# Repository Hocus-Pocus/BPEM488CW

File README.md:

# BPEM488CW
Hardware for the BPEM488CW project

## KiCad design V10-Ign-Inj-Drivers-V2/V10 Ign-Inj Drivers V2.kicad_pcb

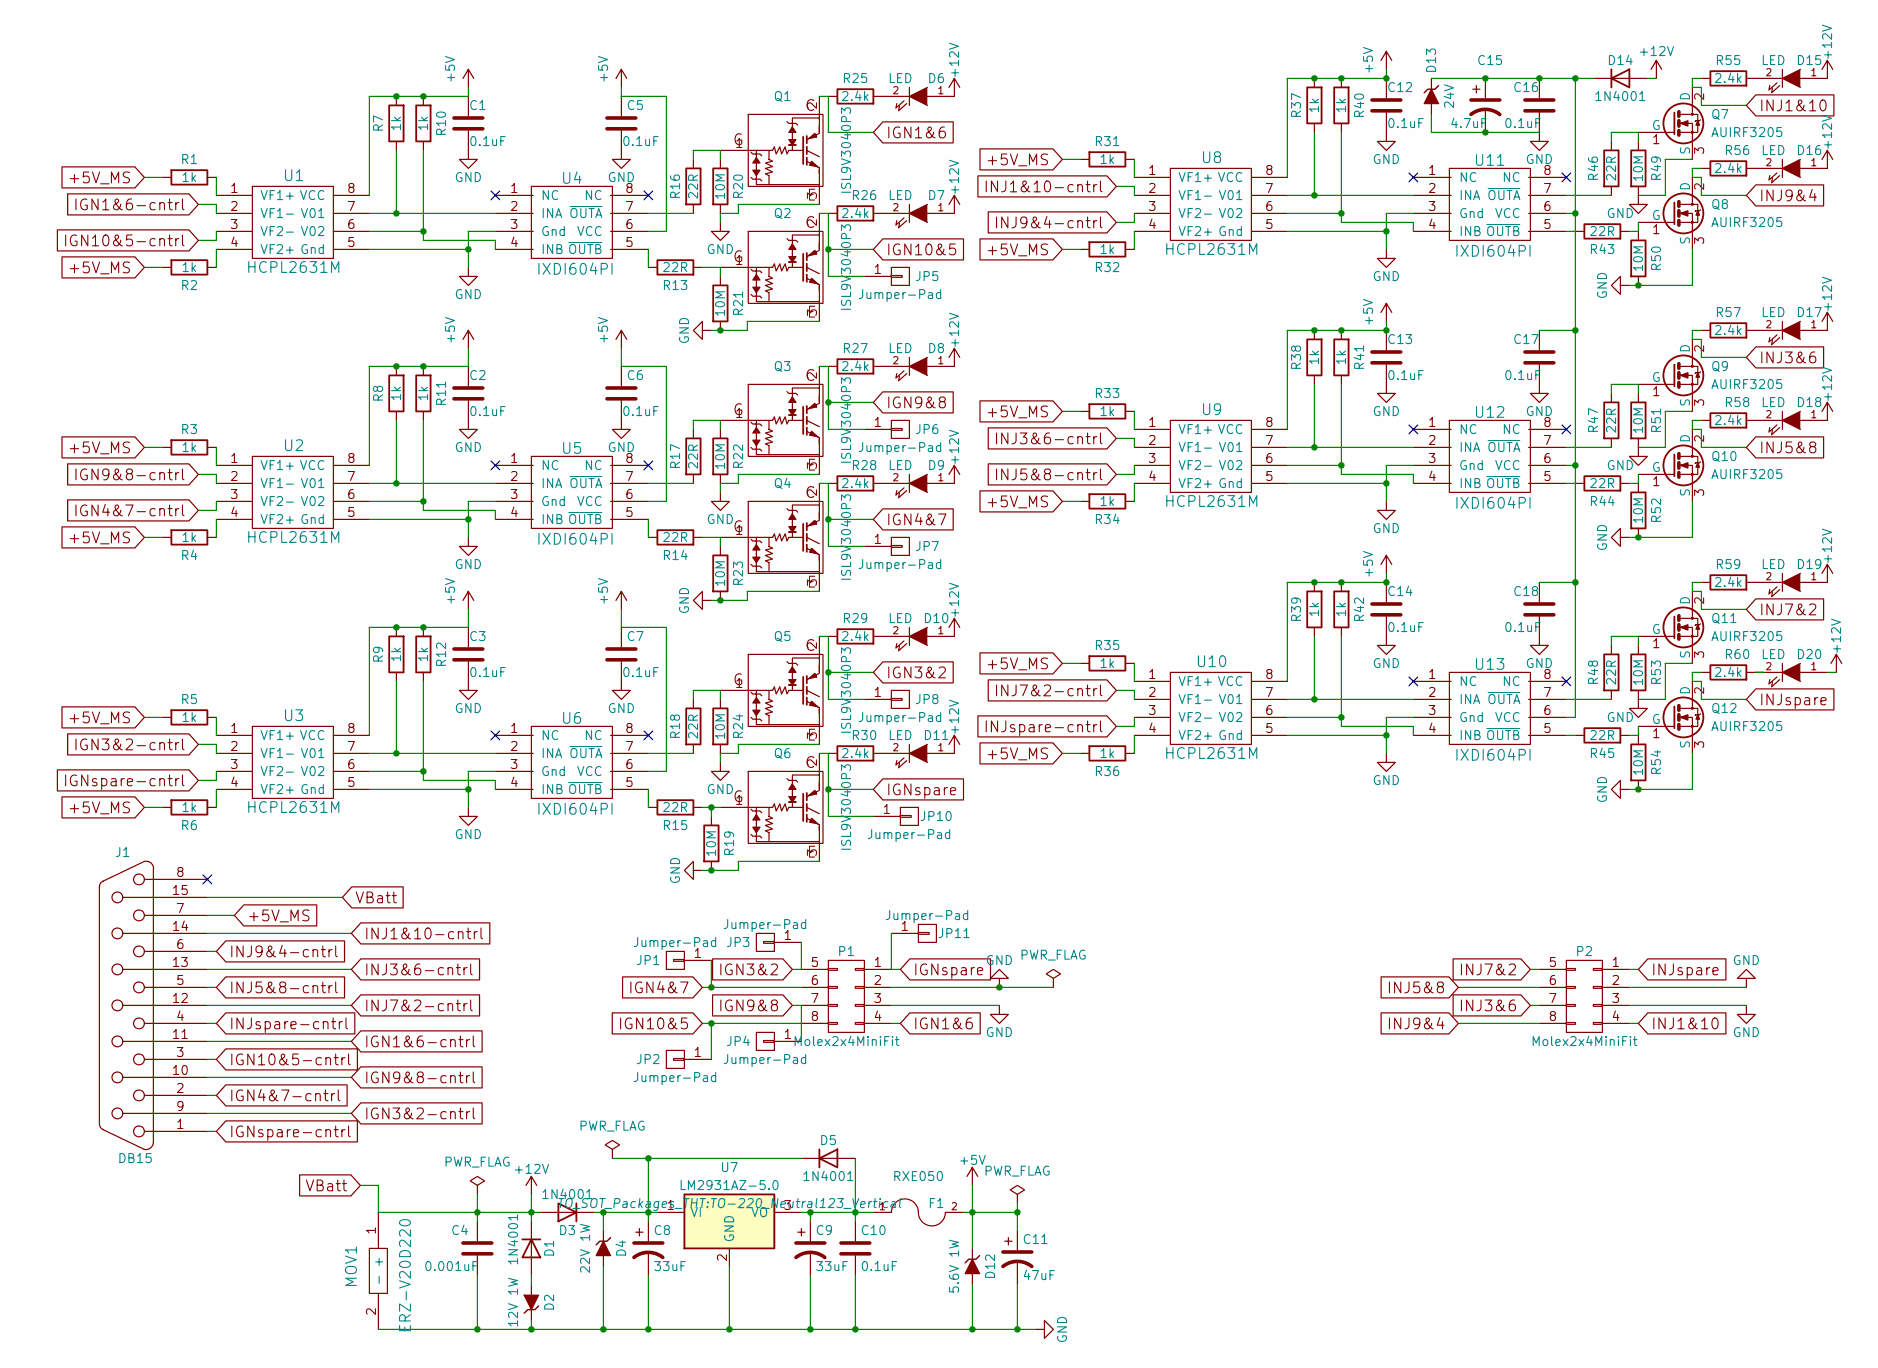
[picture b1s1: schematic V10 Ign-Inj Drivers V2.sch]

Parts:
C1, C2, C3, C5, C6, C7, C10, C12, C13, C14, C16, C17, C18: 0.1uF; C_Disc_D3_P2.5
C4: 0.001uF; C_Disc_D6_P5
C8, C9: 33uF; C_Radial_D10_L13_P5
C11: 47uF; C_Radial_D10_L13_P5
C15: 4.7uF; C_Radial_D5_L6_P2.5
D1, D3, D5, D14: 1N4001; Diode_DO-41_SOD81_Horizontal_RM10
D2: 12V 1W; Diode_DO-41_SOD81_Horizontal_RM10
D4: 22V 1W; Diode_DO-41_SOD81_Horizontal_RM10
D6, D7, D8, D9, D10, D11, D15, D16, D17, D18, D19, D20: LED; LED-3MM
D12: 5.6V 1W; Diode_DO-41_SOD81_Horizontal_RM10
D13: 24V; Diode_DO-41_SOD81_Horizontal_RM10
F1: RXE050; C_Disc_D6_P5
J1: DB15; DB15FC
JP1, JP2, JP3, JP4, JP5, JP6, JP7, JP8, JP10, JP11: Jumper-Pad; 1pin
MOV1: ERZ-V20D220; C_Disc_D3_P2.5
P1, P2: Molex2x4MiniFit; Molex_MiniFit-JR-5569-08A2_2x04x4.20mm_Angled
Q1, Q2, Q3, Q4, Q5, Q6: ISL9V3040P3; TO-220_Neutral123_Vertical
Q7, Q8, Q9, Q10, Q11, Q12: AUIRF3205; TO-220_Neutral123_Vertical
R1, R2, R3, R4, R5, R6, R7, R8, R9, R10, R11, R12, R31, R32, R33, R34, R35, R36, R37, R38, R39, R40, R41, R42: 1k; Resistor_Horizontal_RM7mm
R13, R14, R15, R16, R17, R18, R43, R44, R45, R46, R47, R48: 22R; Resistor_Horizontal_RM10mm
R19, R20, R21, R22, R23, R24, R49, R50, R51, R52, R53, R54: 10M; Resistor_Horizontal_RM7mm
R25, R26, R27, R28, R29, R30, R55, R56, R57, R58, R59, R60: 2.4k; Resistor_Horizontal_RM7mm
U1, U2, U3, U8, U9, U10: HCPL2631M; DIP-8_W7.62mm
U4, U5, U6, U11, U12, U13: IXDI604PI; DIP-8_W7.62mm
U7: LM2931AZ-5.0; TO-220_Neutral123_Vertical

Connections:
+5V: C1.1, C2.1, C3.1, C5.1, C6.1, C7.1, C11.1, C12.1, C13.1, C14.1, D12.1 (K), F1.2, R7.2, R8.2, R9.2, R10.2, R11.2, R12.2, R37.2, R38.2, R39.2, R40.2, R41.2, R42.2, U1.8 (VCC), U2.8 (VCC), U3.8 (VCC), U4.6 (VCC), U5.6 (VCC), U6.6 (VCC), U8.8 (VCC), U9.8 (VCC), U10.8 (VCC)
+5V_MS: J1.7, R1.2, R2.2, R3.2, R4.2, R5.2, R6.2, R31.2, R32.2, R33.2, R34.2, R35.2, R36.2
GND: C1.2, C2.2, C3.2, C4.2, C5.2, C6.2, C7.2, C8.2, C9.2, C10.2, C11.2, C12.2, C13.2, C14.2, C15.2, C16.2, C17.2, C18.2, D2.1 (K), D4.2 (A), D12.2 (A), D13.2 (A), MOV1.2 (-), P1.2, P1.3, P2.2, P2.3, Q1.3 (E), Q2.3 (E), Q3.3 (E), Q4.3 (E), Q5.3 (E), Q6.3 (E), Q7.3 (S), Q8.3 (S), Q9.3 (S), Q10.3 (S), Q11.3 (S), Q12.3 (S), R19.2, R20.2, R21.2, R22.2, R23.2, R24.2, R49.2, R50.2, R51.2, R52.2, R53.2, R54.2, U1.5 (Gnd), U2.5 (Gnd), U3.5 (Gnd), U4.3 (Gnd~), U5.3 (Gnd~), U6.3 (Gnd~), U7.2 (GND), U8.5 (Gnd), U9.5 (Gnd), U10.5 (Gnd), U11.3 (Gnd~), U12.3 (Gnd~), U13.3 (Gnd~)
IGN1&6: P1.4, Q1.2 (C), R25.1
IGN1&6-cntrl: J1.11 (P111), U1.2 (VF1-)
IGN3&2: JP3.1, JP8.1, P1.5, Q5.2 (C), R29.1
IGN3&2-cntrl: J1.9, U3.2 (VF1-)
IGN4&7: JP1.1, JP7.1, P1.6, Q4.2 (C), R28.1
IGN4&7-cntrl: J1.2, U2.3 (VF2-)
IGN9&8: JP4.1, JP6.1, P1.7, Q3.2 (C), R27.1
IGN9&8-cntrl: J1.10, U2.2 (VF1-)
IGN10&5: JP2.1, JP5.1, P1.8, Q2.2 (C), R26.1
IGN10&5-cntrl: J1.3, U1.3 (VF2-)
IGNspare: JP10.1, JP11.1, P1.1, Q6.2 (C), R30.1
IGNspare-cntrl: J1.1, U3.3 (VF2-)
INJ1&10: P2.4, Q7.2 (D), R55.1
INJ1&10-cntrl: J1.14, U8.2 (VF1-)
INJ3&6: P2.7, Q9.2 (D), R57.1
INJ3&6-cntrl: J1.13, U9.2 (VF1-)
INJ5&8: P2.6, Q10.2 (D), R58.1
INJ5&8-cntrl: J1.5, U9.3 (VF2-)
INJ7&2: P2.5, Q11.2 (D), R59.1
INJ7&2-cntrl: J1.12, U10.2 (VF1-)
INJ9&4: P2.8, Q8.2 (D), R56.1
INJ9&4-cntrl: J1.6, U8.3 (VF2-)
INJspare: P2.1, Q12.2 (D), R60.1
INJspare-cntrl: J1.4, U10.3 (VF2-)
unnamed: C8.1, D3.1 (K), D4.1 (K), D5.1 (K), U7.1 (VI)
unnamed: C9.1, C10.1, D5.2 (A), F1.1, U7.3 (VO)
unnamed: C15.1, C16.1, C17.1, C18.1, D13.1 (K), D14.1 (K), U11.6 (VCC), U12.6 (VCC), U13.6 (VCC)
unnamed: D1.2 (A), D2.2 (A)
unnamed: D6.2 (K), R25.2
unnamed: D7.2 (K), R26.2
unnamed: D8.2 (K), R27.2
unnamed: D9.2 (K), R28.2
unnamed: D10.2 (K), R29.2
unnamed: D11.2 (K), R30.2
unnamed: D15.2 (K), R55.2
unnamed: D16.2 (K), R56.2
unnamed: D17.2 (K), R57.2
unnamed: D18.2 (K), R58.2
unnamed: D19.2 (K), R59.2
unnamed: D20.2 (K), R60.2
unnamed: Q1.1 (G), R16.1, R20.1
unnamed: Q2.1 (G), R13.2, R21.1
unnamed: Q3.1 (G), R17.1, R22.1
unnamed: Q4.1 (G), R14.2, R23.1
unnamed: Q5.1 (G), R18.1, R24.1
unnamed: Q6.1 (G), R15.2, R19.1
unnamed: Q7.1 (G), R46.1, R49.1
unnamed: Q8.1 (G), R43.2, R50.1
unnamed: Q9.1 (G), R47.1, R51.1
unnamed: Q10.1 (G), R44.2, R52.1
unnamed: Q11.1 (G), R48.1, R53.1
unnamed: Q12.1 (G), R45.2, R54.1
unnamed: R1.1, U1.1 (VF1+)
unnamed: R2.1, U1.4 (VF2+)
unnamed: R3.1, U2.1 (VF1+)
unnamed: R4.1, U2.4 (VF2+)
unnamed: R5.1, U3.1 (VF1+)
unnamed: R6.1, U3.4 (VF2+)
unnamed: R7.1, U1.7 (V01), U4.2 (INA)
unnamed: R8.1, U2.7 (V01), U5.2 (INA)
unnamed: R9.1, U3.7 (V01), U6.2 (INA)
unnamed: R10.1, U1.6 (V02), U4.4 (INB)
unnamed: R11.1, U2.6 (V02), U5.4 (INB)
unnamed: R12.1, U3.6 (V02), U6.4 (INB)
unnamed: R13.1, U4.5 (~OUTB)
unnamed: R14.1, U5.5 (~OUTB)
unnamed: R15.1, U6.5 (~OUTB)
unnamed: R16.2, U4.7 (~OUTA)
unnamed: R17.2, U5.7 (~OUTA)
unnamed: R18.2, U6.7 (~OUTA)
unnamed: R31.1, U8.1 (VF1+)
unnamed: R32.1, U8.4 (VF2+)
unnamed: R33.1, U9.1 (VF1+)
unnamed: R34.1, U9.4 (VF2+)
unnamed: R35.1, U10.1 (VF1+)
unnamed: R36.1, U10.4 (VF2+)
unnamed: R37.1, U8.7 (V01), U11.2 (INA)
unnamed: R38.1, U9.7 (V01), U12.2 (INA)
unnamed: R39.1, U10.7 (V01), U13.2 (INA)
unnamed: R40.1, U8.6 (V02), U11.4 (INB)
unnamed: R41.1, U9.6 (V02), U12.4 (INB)
unnamed: R42.1, U10.6 (V02), U13.4 (INB)
unnamed: R43.1, U11.5 (~OUTB)
unnamed: R44.1, U12.5 (~OUTB)
unnamed: R45.1, U13.5 (~OUTB)
unnamed: R46.2, U11.7 (~OUTA)
unnamed: R47.2, U12.7 (~OUTA)
unnamed: R48.2, U13.7 (~OUTA)
VBatt: C4.1, D1.1 (K), D3.2 (A), D6.1 (A), D7.1 (A), D8.1 (A), D9.1 (A), D10.1 (A), D11.1 (A), D14.2 (A), D15.1 (A), D16.1 (A), D17.1 (A), D18.1 (A), D19.1 (A), D20.1 (A), J1.15, MOV1.1 (+)

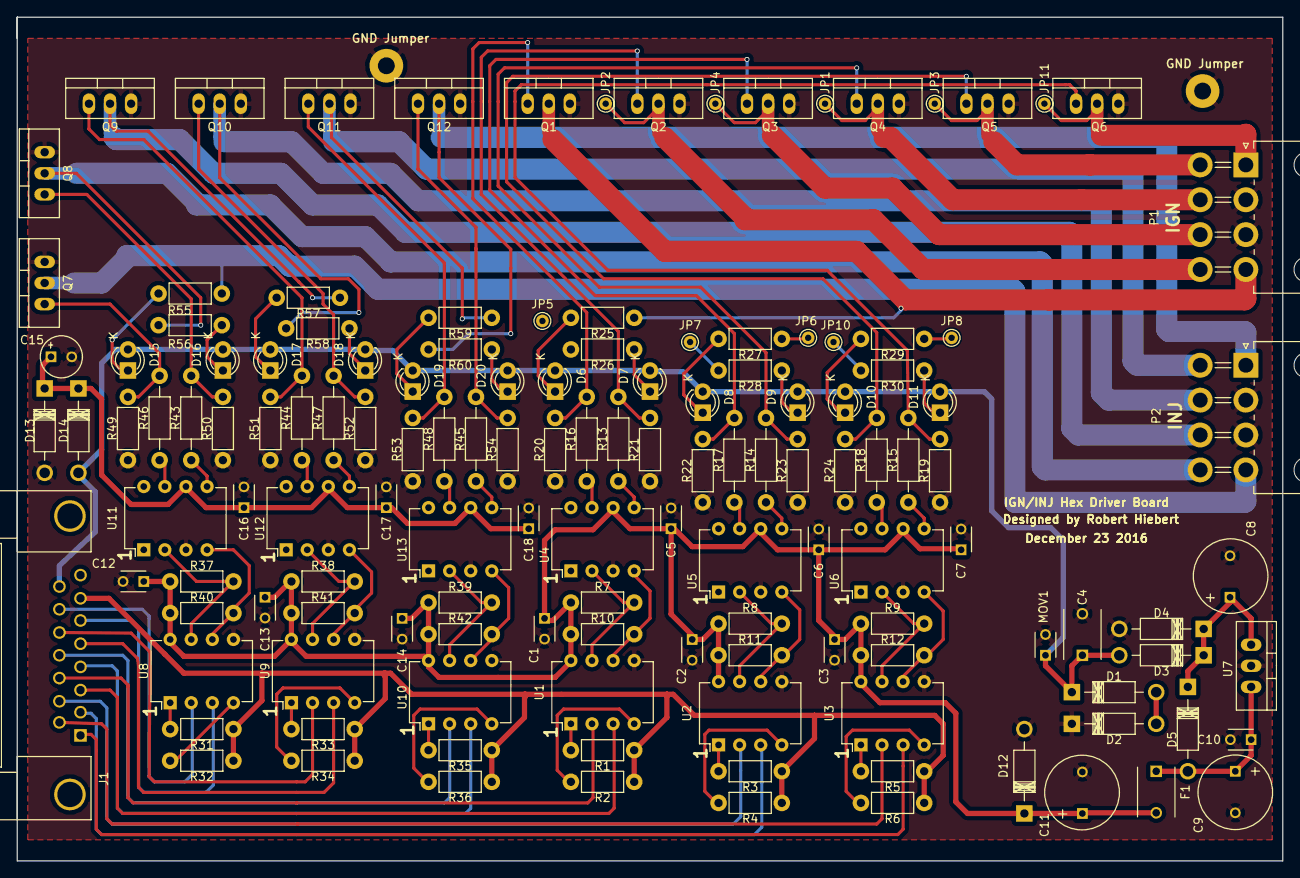
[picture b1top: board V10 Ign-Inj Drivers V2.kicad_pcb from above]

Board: 2 copper layers, 152.4 x 101.6 mm, 138 parts (0 on the bottom side), 92 nets.

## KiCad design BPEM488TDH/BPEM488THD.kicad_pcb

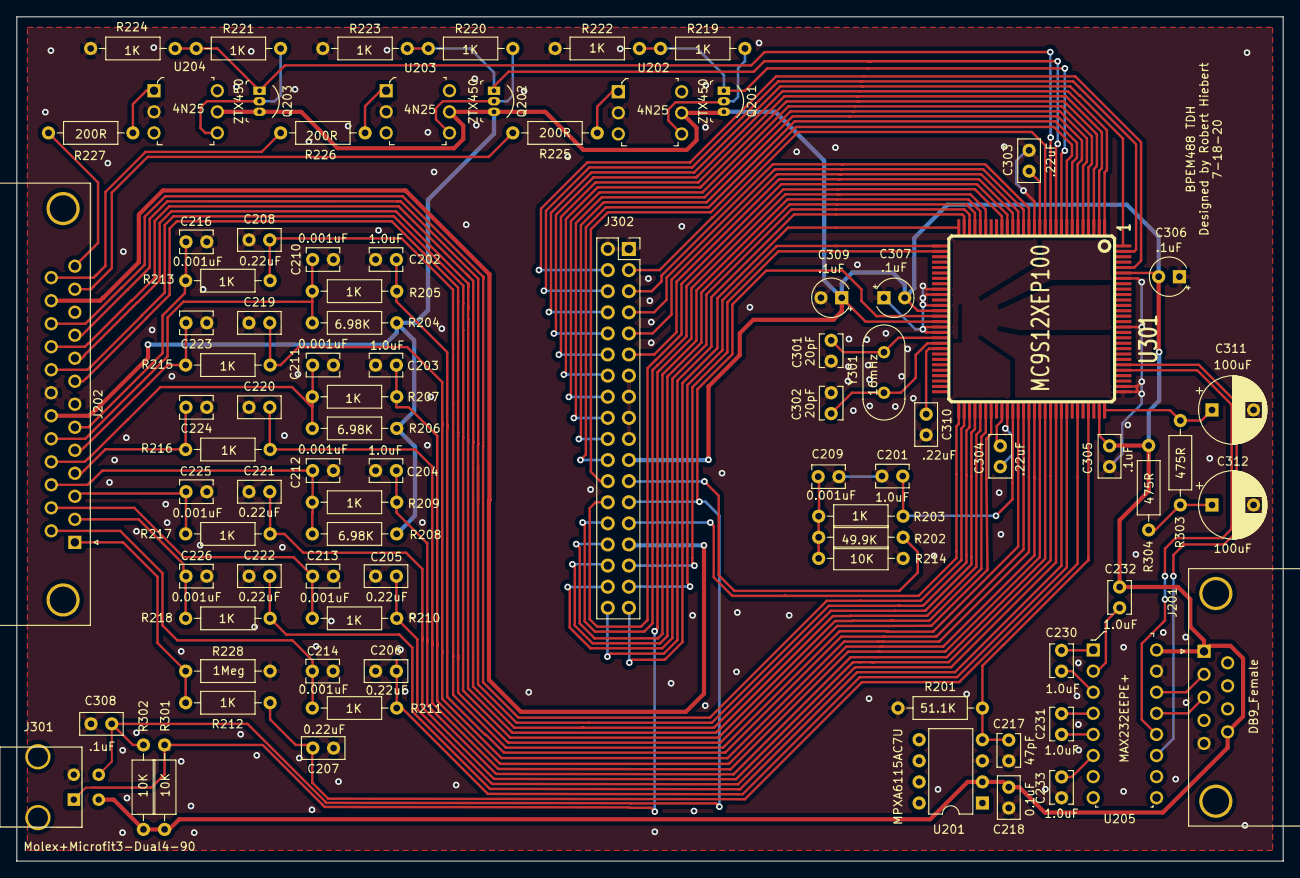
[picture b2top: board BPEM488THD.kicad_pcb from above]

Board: 2 copper layers, 152.4 x 101.6 mm, 87 parts (0 on the bottom side), 92 nets.

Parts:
C201, C202, C203, C204, C230, C231, C232, C233: 1.0uF; C_Disc_D3.8mm_W2.6mm_P2.50mm
C205, C206, C207, C208, C219, C220, C221, C222: 0.22uF; C_Disc_D5.0mm_W2.5mm_P2.50mm
C209, C210, C211, C212, C213, C214, C216, C223, C224, C225, C226: 0.001uF; C_Disc_D3.8mm_W2.6mm_P2.50mm
C217: 47pF; C_Disc_D3.8mm_W2.6mm_P2.50mm
C218: 0.1uF; C_Disc_D5.0mm_W2.5mm_P2.50mm
C301, C302: 20pF; C_Disc_D3.8mm_W2.6mm_P2.50mm
C303, C304, C310: .22uF; C_Disc_D5.0mm_W2.5mm_P2.50mm
C305, C308: .1uF; C_Disc_D5.0mm_W2.5mm_P2.50mm
C306, C307, C309: .1uF; CP_Radial_Tantal_D4.5mm_P2.50mm
C311, C312: 100uF; CP_Radial_D8.0mm_P5.00mm
J201: DB9_Female; DSUB-9_Female_Horizontal_P2.77x2.84mm_EdgePinOffset9.90mm_H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
J202: DB25_Female; DSUB-25_Female_Horizontal_P2.77x2.84mm_EdgePinOffset7.70mm_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
J301: Molex+Microfit3-Dual4-90; Molex-Microfit3-Dual4-90
J302: Conn_02x18_Odd_Even; PinSocket_2x18_P2.54mm_Vertical
Q201, Q202, Q203: ZTX450; TO-92-3
R201: 51.1K; R_Axial_DIN0207_L6.3mm_D2.5mm_P10.16mm_Horizontal
R202: 49.9K; R_Axial_DIN0207_L6.3mm_D2.5mm_P10.16mm_Horizontal
R203, R205, R207, R209, R210, R211, R212, R213, R215, R216, R217, R218, R219, R220, R221, R222, R223, R224: 1K; R_Axial_DIN0207_L6.3mm_D2.5mm_P10.16mm_Horizontal
R204, R206, R208: 6.98K; R_Axial_DIN0207_L6.3mm_D2.5mm_P10.16mm_Horizontal
R214, R301, R302: 10K; R_Axial_DIN0207_L6.3mm_D2.5mm_P10.16mm_Horizontal
R225, R226, R227: 200R; R_Axial_DIN0207_L6.3mm_D2.5mm_P10.16mm_Horizontal
R228: 1Meg; R_Axial_DIN0207_L6.3mm_D2.5mm_P10.16mm_Horizontal
R303, R304: 475R; R_Axial_DIN0207_L6.3mm_D2.5mm_P10.16mm_Horizontal
U201: MPXA6115AC7U; DIP-8_W7.62mm
U202, U203, U204: 4N25; DIP-6_W7.62mm
U205: MAX232EEPE+; DIP-16_W7.62mm
U301: MC9S12XEP100; PQFP112
Y301: 16mHz; Crystal_HC49-4H_Vertical

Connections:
+8V: J202.24, J302.29
+BATT: J302.23, R202.2
/CPU/PA0: J302.27, U301.57
/CPU/PB0: J302.30, U301.24
/CPU/PB1: J302.32, U301.25
/CPU/PB2: J302.34, U301.26
/CPU/PB3: J302.36, U301.27
/CPU/PB4: J302.35, U301.28
/CPU/PB5: J302.33, U301.29
/CPU/PB6: J302.31, U301.30
/CPU/PK0: J302.24, U301.8
/CPU/PK1: J302.22, U301.7
/CPU/PK2: J302.20, U301.6
/CPU/PK3: J302.18, U301.5
/CPU/PK4: J302.28, U301.20
/CPU/PK5: J302.26, U301.19
/CPU/PK7: J302.4, U301.108
/CPU/PP0: J302.16, U301.4
/CPU/PP1: J302.14, U301.3
/CPU/PP2: J302.12, U301.2
/CPU/PP3: J302.10, U301.1
/CPU/PP4: J302.8, U301.112
/CPU/PP5: J302.6, U301.111
/CPU/PT3: J302.3, U301.12
/CPU/PT4: J302.5, U301.15
/CPU/PT5: J302.7, U301.16
/CPU/PT6: J302.9, U301.17
/CPU/PT7: J302.11, U301.18
/CPU/RESET: C308.1, J301.4, J302.25, R302.2, U301.42
/Inputs_RS232/CKP: J202.25, R226.1
/Inputs_RS232/CLT: C210.2, J202.18, R204.1, R205.1
/Inputs_RS232/CMP: J202.12, R225.1
/Inputs_RS232/EFP: C223.2, J202.5, R215.1
/Inputs_RS232/EGO: J202.1, R212.1, R228.1
/Inputs_RS232/EOP: C216.2, J202.6, R213.1
/Inputs_RS232/Ftrm: C225.2, J202.3, R217.1
/Inputs_RS232/Itrm: C224.2, J202.4, R216.1
/Inputs_RS232/MAP: C213.2, J202.15, R210.1
/Inputs_RS232/MAT: C211.2, J202.17, R206.1, R207.1
/Inputs_RS232/PAD03in: C212.2, J202.16, R208.1, R209.1
/Inputs_RS232/PAD12in: C226.2, J202.2, R218.1
/Inputs_RS232/TPS: C214.2, J202.14, R211.1
/Inputs_RS232/VSPD: J202.13, R227.1
GND: C201.1, C202.1, C203.1, C204.1, C205.1, C206.1, C207.1, C208.1, C209.1, C210.1, C211.1, C212.1, C213.1, C214.1, C216.1, C217.1, C218.2, C219.1, C220.1, C221.1, C222.1, C223.1, C224.1, C225.1, C226.1, C233.1, C301.1, C302.1, C303.1, C304.1, C305.1, C306.1, C307.1, C308.2, C309.2, C310.2, C311.2, C312.2, J201.5, J202.7, J202.11, J202.20, J301.2, J302.1, J302.2, J302.13, J302.15, J302.17, J302.19, R201.2, R214.1, R222.1, R223.1, R224.1, R228.2, U201.3, U202.2, U203.2, U204.2, U205.15, U301.14, U301.37, U301.38, U301.40, U301.44, U301.45, U301.66, U301.85, U301.86, U301.97, U301.106
unnamed: C209.2, R202.1, R203.1, R214.2
unnamed: C230.1, U205.3
unnamed: C230.2, U205.1
unnamed: C231.1, U205.5
unnamed: C231.2, U205.4
unnamed: C232.1, U205.2
unnamed: C233.2, U205.6
unnamed: C301.2, U301.46, Y301.2
unnamed: C302.2, U301.47, Y301.1
unnamed: C303.2, U301.13
unnamed: C304.2, U301.65
unnamed: C310.1, U301.48
unnamed: C311.1, R303.1, U301.84
unnamed: C312.1, R303.2, R304.1
unnamed: J201.2, U205.14
unnamed: J201.3, U205.13
unnamed: J301.1, R301.2, U301.23
unnamed: Q201.2, R219.2, U202.4
unnamed: Q202.2, R220.2, U203.4
unnamed: Q203.2, R221.2, U204.4
unnamed: R225.2, U202.1
unnamed: R226.2, U203.1
unnamed: R227.2, U204.1
PA1: J202.23, U301.58
PA2: J202.10, U301.59
PA3: J202.22, U301.60
PA4: J202.9, U301.61
PA5: J202.21, U301.62
PA6: J202.8, U301.63
PAD00: C201.2, R203.2, U301.67
PAD01: C202.2, R205.2, U301.69
PAD02: C203.2, R207.2, U301.71
PAD03: C204.2, R209.2, U301.73
PAD04: C205.2, R210.2, U301.75
PAD05: C206.2, R211.2, U301.77
PAD06: C207.2, R212.2, U301.79
PAD07: C217.2, R201.1, U201.4, U301.81
PAD08: C208.2, R213.2, U301.68
PAD09: C219.2, R215.2, U301.70
PAD10: C220.2, R216.2, U301.72
PAD11: C221.2, R217.2, U301.74
PAD12: C222.2, R218.2, U301.76
PS0: U205.12, U301.89
PS1: U205.11, U301.90
PT0: Q201.1, R219.1, R222.2, U301.9
PT1: Q202.1, R220.1, R223.2, U301.10
PT2: Q203.1, R221.1, R224.2, U301.11
VDD: C218.1, C232.2, C305.2, C306.2, C307.2, C309.1, J201.1, J201.9, J202.19, J301.3, J302.21, Q201.3, Q202.3, Q203.3, R204.2, R206.2, R208.2, R301.1, R302.1, R304.2, U201.2, U202.5, U203.5, U204.5, U205.16, U301.41, U301.43, U301.83, U301.107

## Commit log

2022-11-15 Create Git Hold
